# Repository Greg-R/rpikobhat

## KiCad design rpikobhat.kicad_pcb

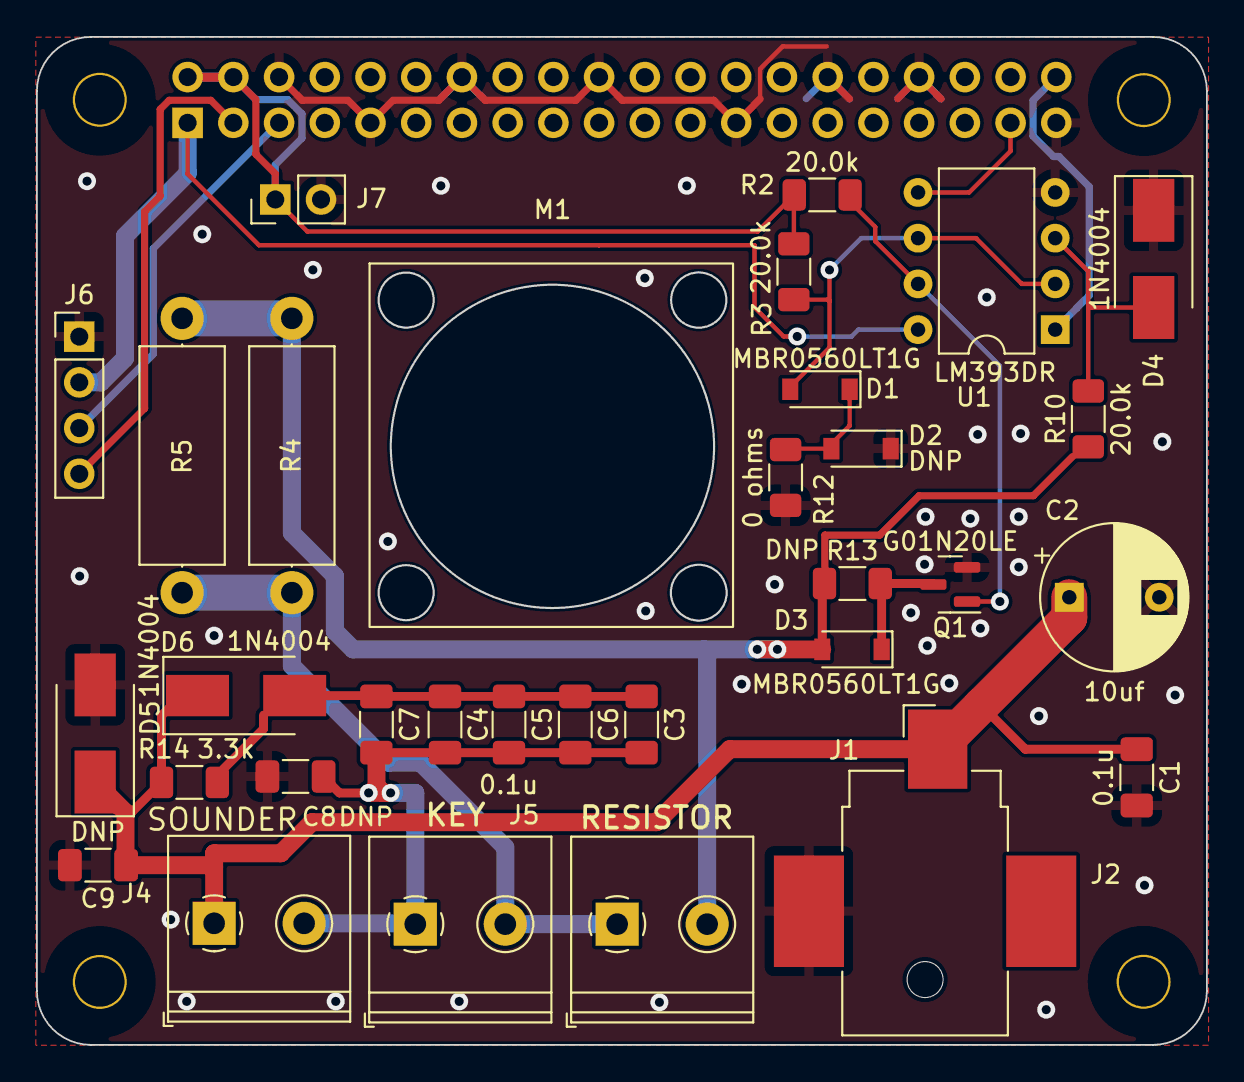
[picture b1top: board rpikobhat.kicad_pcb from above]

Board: 2 copper layers, 65.0 x 56.0 mm, 37 parts (1 on the bottom side), 17 nets.

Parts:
C1, C3, C4, C5, C6, C7: 0.1u; C_1206_3216Metric_Pad1.33x1.80mm_HandSolder
C2: 10uf; CP_Radial_D8.0mm_P5.00mm
C8, C9: DNP; C_1206_3216Metric_Pad1.33x1.80mm_HandSolder
D1, D3: MBR0560LT1G; D_SOD-123
D2: DNP; D_SOD-123
D4, D5, D6: 1N4004; D_SMB_Handsoldering
H1, H2, H3, H4: 3mm_Mounting_Hole; NPTH_3mm_ID
J1: Conn_Coaxial_Power; BarrelJack_CUI_PJ-036AH-SMT_Horizontal
J2, J4, J5: Screw_Terminal_01x02; TerminalBlock_Philmore_TB132_1x02_P5.00mm_Horizontal
J3: PI40HAT; PinSocket_2x20_P2.54mm_Vertical
J6: Conn_01x04; PinHeader_1x04_P2.54mm_Vertical
J7: Conn_01x02; PinHeader_1x02_P2.54mm_Vertical
M1: Fan; FAN_20mm
Q1: G01N20LE; SOT-23
R2, R3, R10: 20.0k; R_1206_3216Metric_Pad1.30x1.75mm_HandSolder
R4, R5: R_US; R_Axial_DIN0414_L11.9mm_D4.5mm_P15.24mm_Horizontal
R12: 0 ohms; R_1206_3216Metric_Pad1.30x1.75mm_HandSolder
R13: DNP; R_1206_3216Metric_Pad1.30x1.75mm_HandSolder
R14: 3.3k; R_1206_3216Metric_Pad1.30x1.75mm_HandSolder
U1: LM393DR; DIP-8_W7.62mm

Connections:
/GPI21: J3.40 (BCM21), U1.1 (1OUT)
/GPO26: J3.37 (BCM26), U1.5 (2IN+)
/LOOP_STATE: D3.2 (A), J2.2, R4.2, R5.2, R10.1, R13.1
/OFFSET_REF_V: D1.2 (A), R3.2, U1.2, U1.6 (2IN-)
/P3V3_HAT: J3.1 (P3V3), J6.2, U1.8 (VCC)
/P5V_HAT: J3.2 (P5V), J3.4 (P5V), J7.1, R2.2, R3.1
/SCL: J3.5 (BCM3), J6.3
/SDA: J3.3 (BCM2), J6.4
GND: C1.2, C2.2, C8.2, C9.2, D2.1 (K), D4.1 (K), D5.2 (A), J1.2 (Ext), J3.6 (GND), J3.9 (GND), J3.14 (GND), J3.20 (GND), J3.25 (GND), J3.30 (GND), J3.34 (GND), J3.39 (GND), J6.1, J7.2, Q1.2 (S), R12.2, U1.4 (GND)
unnamed: C1.1, C2.1, C9.1, D5.1 (K), D6.1 (K), J1.1 (In), J4.1, R14.1
unnamed: C3.1, C4.1, C5.1, C6.1, C7.1, D6.2 (A), R14.2
unnamed: C3.2, C4.2, C5.2, C6.2, C7.2, C8.1, J4.2, J5.1
unnamed: D1.1 (K), D2.2 (A), R12.1
unnamed: D3.1 (K), Q1.3 (D), R13.2
unnamed: D4.2 (A), R10.2, U1.3
unnamed: J2.1, J5.2, R4.1, R5.1
unnamed: Q1.1 (G), R2.1, U1.7 (2OUT)

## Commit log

2022-03-21 Initial commit.
2022-03-21 First commit after making pchannel branch
2022-03-24 Mostly done. Need to check gerbers.
2022-04-05 PCB version 1.0 complete.
2022-04-13 Added .gitignore
2022-04-14 Added a few notes to schematic.
2022-04-27 Added snubber to sounder.
2022-05-19 Minor changes to notes on schematic.
2022-05-20 Added fan, I2C port, and snubber. General clean-up.
2022-05-20 Added snubber, 20mm fan, I2C port, and more decoupling caps for sounder.
